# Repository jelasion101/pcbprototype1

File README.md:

Uses footprints sourced from Joe Scotto https://github.com/joe-scotto/, find sourced footprints at https://github.com/joe-scotto/scottokeebs

jelaskeyboard.kicad_pcb: KICAD PCB Design

jelaskeyboard.kicad_sch: KICAD Schematic Diagram + Footprints

jelaskeyboard.kicad_prl / jelaskeyboard.kicad_pro: Associated KICAD files

jelaskeyboard.zip: Built GBR ZIP file

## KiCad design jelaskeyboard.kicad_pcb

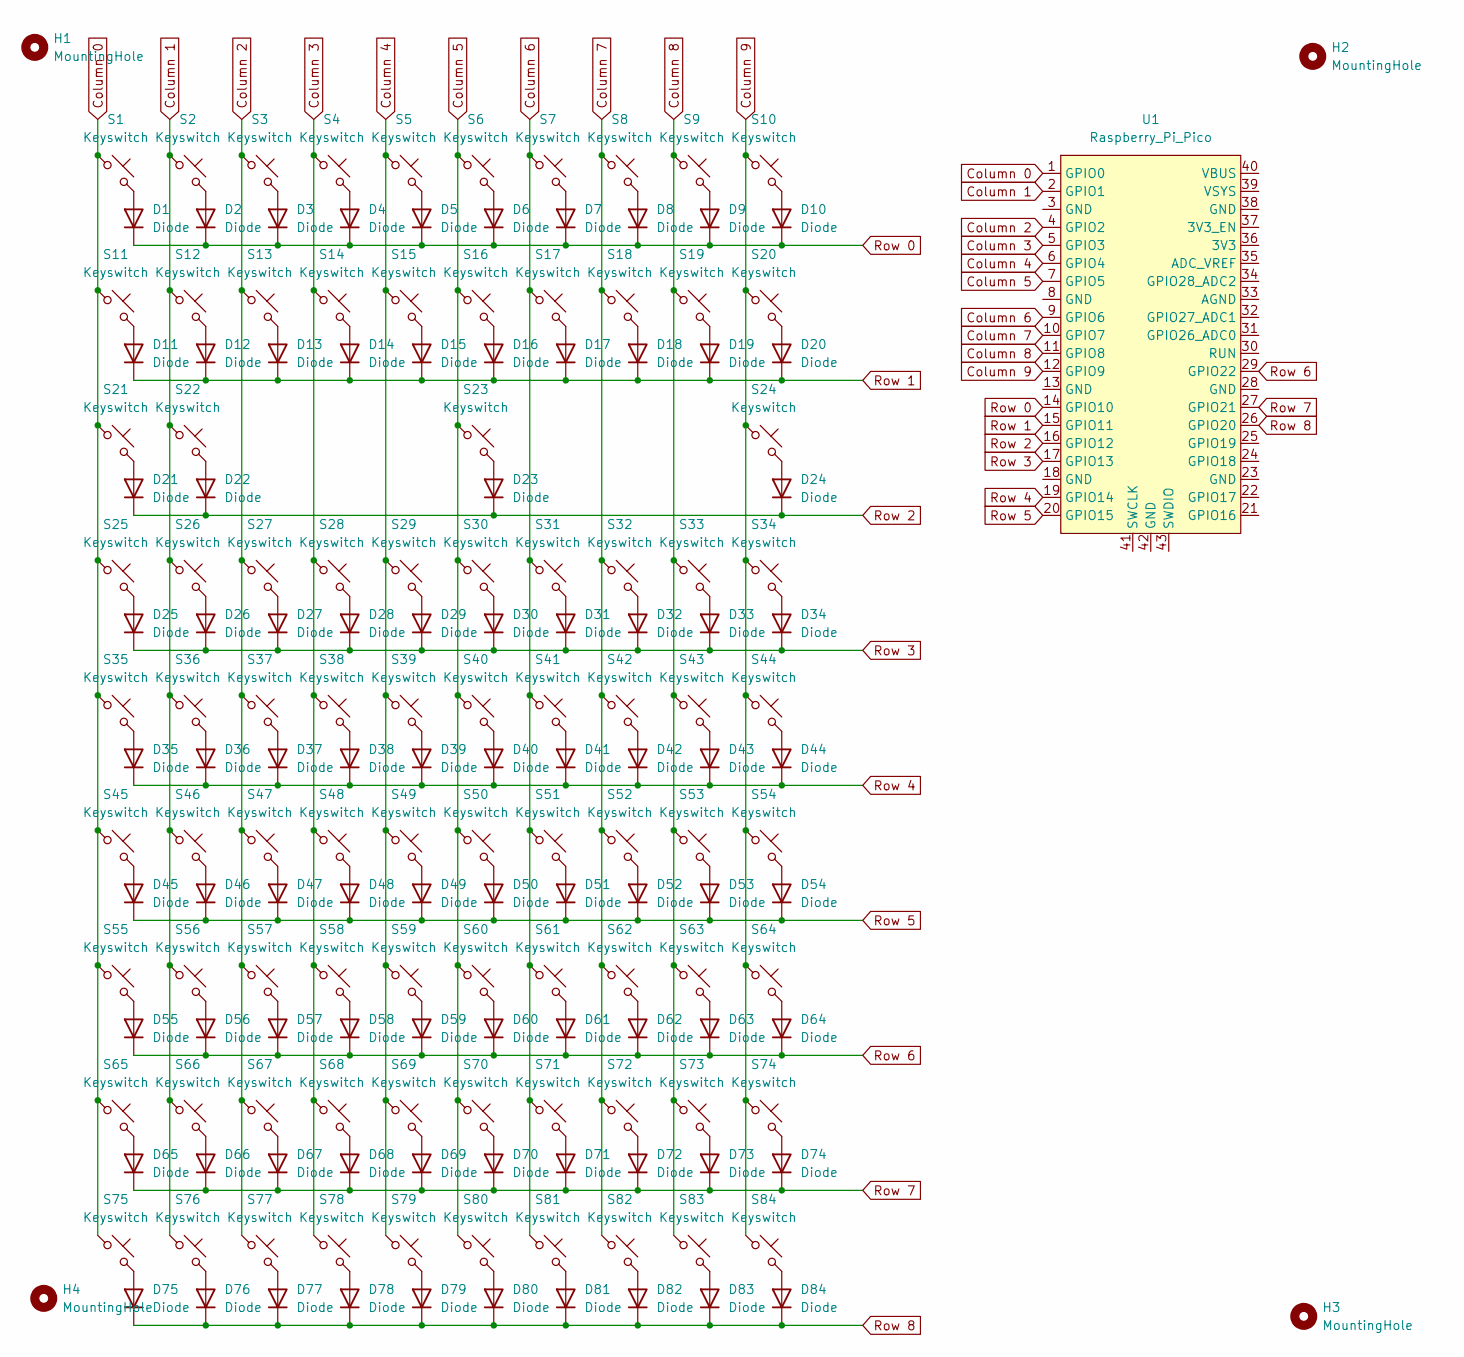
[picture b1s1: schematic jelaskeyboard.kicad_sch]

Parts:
D1, D2, D3, D4, D5, D6, D7, D8, D9, D10, D11, D12, D13, D14, D15, D16, D17, D18, D19, D20, D21, D22, D23, D24, D25, D26, D27, D28, D29, D30, D31, D32, D33, D34, D35, D36, D37, D38, D39, D40, D41, D42, D43, D44, D45, D46, D47, D48, D49, D50, D51, D52, D53, D54, D55, D56, D57, D58, D59, D60, D61, D62, D63, D64, D65, D66, D67, D68, D69, D70, D71, D72, D73, D74, D75, D76, D77, D78, D79, D80, D81, D82, D83, D84: Diode; Diode_DO-35
H1, H2, H3, H4: MountingHole; MountingHole_2.1mm
S1, S2, S3, S4, S5, S6, S7, S8, S9, S10, S11, S12, S13, S14, S15, S16, S17, S18, S19, S20, S22, S25, S26, S27, S28, S29, S30, S31, S32, S33, S34, S35, S36, S37, S38, S39, S40, S41, S42, S43, S44, S45, S46, S47, S48, S49, S50, S51, S52, S53, S54, S55, S56, S57, S58, S59, S60, S61, S62, S63, S64, S65, S66, S67, S68, S69, S70, S71, S72, S73, S74, S75, S76, S77, S78, S79, S80, S81, S82, S83, S84: Keyswitch; MX_PCB_1.00u
S21, S24: Keyswitch; MX_PCB_1.50u
S23: Keyswitch; MX_PCB_6.00u
U1: Raspberry_Pi_Pico

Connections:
Column 0: S1.1, S11.1, S21.1, S25.1, S35.1, S45.1, S55.1, S65.1, S75.1, U1.1 (GPIO0)
Column 1: S2.1, S12.1, S22.1, S26.1, S36.1, S46.1, S56.1, S66.1, S76.1, U1.2 (GPIO1)
Column 2: S3.1, S13.1, S27.1, S37.1, S47.1, S57.1, S67.1, S77.1, U1.4 (GPIO2)
Column 3: S4.1, S14.1, S28.1, S38.1, S48.1, S58.1, S68.1, S78.1, U1.5 (GPIO3)
Column 4: S5.1, S15.1, S29.1, S39.1, S49.1, S59.1, S69.1, S79.1, U1.6 (GPIO4)
Column 5: S6.1, S16.1, S23.1, S30.1, S40.1, S50.1, S60.1, S70.1, S80.1, U1.7 (GPIO5)
Column 6: S7.1, S17.1, S31.1, S41.1, S51.1, S61.1, S71.1, S81.1, U1.9 (GPIO6)
Column 7: S8.1, S18.1, S32.1, S42.1, S52.1, S62.1, S72.1, S82.1, U1.10 (GPIO7)
Column 8: S9.1, S19.1, S33.1, S43.1, S53.1, S63.1, S73.1, S83.1, U1.11 (GPIO8)
Column 9: S10.1, S20.1, S24.1, S34.1, S44.1, S54.1, S64.1, S74.1, S84.1, U1.12 (GPIO9)
unnamed: D1.2 (A), S1.2
unnamed: D2.2 (A), S2.2
unnamed: D3.2 (A), S3.2
unnamed: D4.2 (A), S4.2
unnamed: D5.2 (A), S5.2
unnamed: D6.2 (A), S6.2
unnamed: D7.2 (A), S7.2
unnamed: D8.2 (A), S8.2
unnamed: D9.2 (A), S9.2
unnamed: D10.2 (A), S10.2
unnamed: D11.2 (A), S11.2
unnamed: D12.2 (A), S12.2
unnamed: D13.2 (A), S13.2
unnamed: D14.2 (A), S14.2
unnamed: D15.2 (A), S15.2
unnamed: D16.2 (A), S16.2
unnamed: D17.2 (A), S17.2
unnamed: D18.2 (A), S18.2
unnamed: D19.2 (A), S19.2
unnamed: D20.2 (A), S20.2
unnamed: D21.2 (A), S21.2
unnamed: D22.2 (A), S22.2
unnamed: D23.2 (A), S23.2
unnamed: D24.2 (A), S24.2
unnamed: D25.2 (A), S25.2
unnamed: D26.2 (A), S26.2
unnamed: D27.2 (A), S27.2
unnamed: D28.2 (A), S28.2
unnamed: D29.2 (A), S29.2
unnamed: D30.2 (A), S30.2
unnamed: D31.2 (A), S31.2
unnamed: D32.2 (A), S32.2
unnamed: D33.2 (A), S33.2
unnamed: D34.2 (A), S34.2
unnamed: D35.2 (A), S35.2
unnamed: D36.2 (A), S36.2
unnamed: D37.2 (A), S37.2
unnamed: D38.2 (A), S38.2
unnamed: D39.2 (A), S39.2
unnamed: D40.2 (A), S40.2
unnamed: D41.2 (A), S41.2
unnamed: D42.2 (A), S42.2
unnamed: D43.2 (A), S43.2
unnamed: D44.2 (A), S44.2
unnamed: D45.2 (A), S45.2
unnamed: D46.2 (A), S46.2
unnamed: D47.2 (A), S47.2
unnamed: D48.2 (A), S48.2
unnamed: D49.2 (A), S49.2
unnamed: D50.2 (A), S50.2
unnamed: D51.2 (A), S51.2
unnamed: D52.2 (A), S52.2
unnamed: D53.2 (A), S53.2
unnamed: D54.2 (A), S54.2
unnamed: D55.2 (A), S55.2
unnamed: D56.2 (A), S56.2
unnamed: D57.2 (A), S57.2
unnamed: D58.2 (A), S58.2
unnamed: D59.2 (A), S59.2
unnamed: D60.2 (A), S60.2
unnamed: D61.2 (A), S61.2
unnamed: D62.2 (A), S62.2
unnamed: D63.2 (A), S63.2
unnamed: D64.2 (A), S64.2
unnamed: D65.2 (A), S65.2
unnamed: D66.2 (A), S66.2
unnamed: D67.2 (A), S67.2
unnamed: D68.2 (A), S68.2
unnamed: D69.2 (A), S69.2
unnamed: D70.2 (A), S70.2
unnamed: D71.2 (A), S71.2
unnamed: D72.2 (A), S72.2
unnamed: D73.2 (A), S73.2
unnamed: D74.2 (A), S74.2
unnamed: D75.2 (A), S75.2
unnamed: D76.2 (A), S76.2
unnamed: D77.2 (A), S77.2
unnamed: D78.2 (A), S78.2
unnamed: D79.2 (A), S79.2
unnamed: D80.2 (A), S80.2
unnamed: D81.2 (A), S81.2
unnamed: D82.2 (A), S82.2
unnamed: D83.2 (A), S83.2
unnamed: D84.2 (A), S84.2
Row 0: D1.1 (K), D2.1 (K), D3.1 (K), D4.1 (K), D5.1 (K), D6.1 (K), D7.1 (K), D8.1 (K), D9.1 (K), D10.1 (K), U1.14 (GPIO10)
Row 1: D11.1 (K), D12.1 (K), D13.1 (K), D14.1 (K), D15.1 (K), D16.1 (K), D17.1 (K), D18.1 (K), D19.1 (K), D20.1 (K), U1.15 (GPIO11)
Row 2: D21.1 (K), D22.1 (K), D23.1 (K), D24.1 (K), U1.16 (GPIO12)
Row 3: D25.1 (K), D26.1 (K), D27.1 (K), D28.1 (K), D29.1 (K), D30.1 (K), D31.1 (K), D32.1 (K), D33.1 (K), D34.1 (K), U1.17 (GPIO13)
Row 4: D35.1 (K), D36.1 (K), D37.1 (K), D38.1 (K), D39.1 (K), D40.1 (K), D41.1 (K), D42.1 (K), D43.1 (K), D44.1 (K), U1.19 (GPIO14)
Row 5: D45.1 (K), D46.1 (K), D47.1 (K), D48.1 (K), D49.1 (K), D50.1 (K), D51.1 (K), D52.1 (K), D53.1 (K), D54.1 (K), U1.20 (GPIO15)
Row 6: D55.1 (K), D56.1 (K), D57.1 (K), D58.1 (K), D59.1 (K), D60.1 (K), D61.1 (K), D62.1 (K), D63.1 (K), D64.1 (K), U1.29 (GPIO22)
Row 7: D65.1 (K), D66.1 (K), D67.1 (K), D68.1 (K), D69.1 (K), D70.1 (K), D71.1 (K), D72.1 (K), D73.1 (K), D74.1 (K), U1.27 (GPIO21)
Row 8: D75.1 (K), D76.1 (K), D77.1 (K), D78.1 (K), D79.1 (K), D80.1 (K), D81.1 (K), D82.1 (K), D83.1 (K), D84.1 (K), U1.26 (GPIO20)

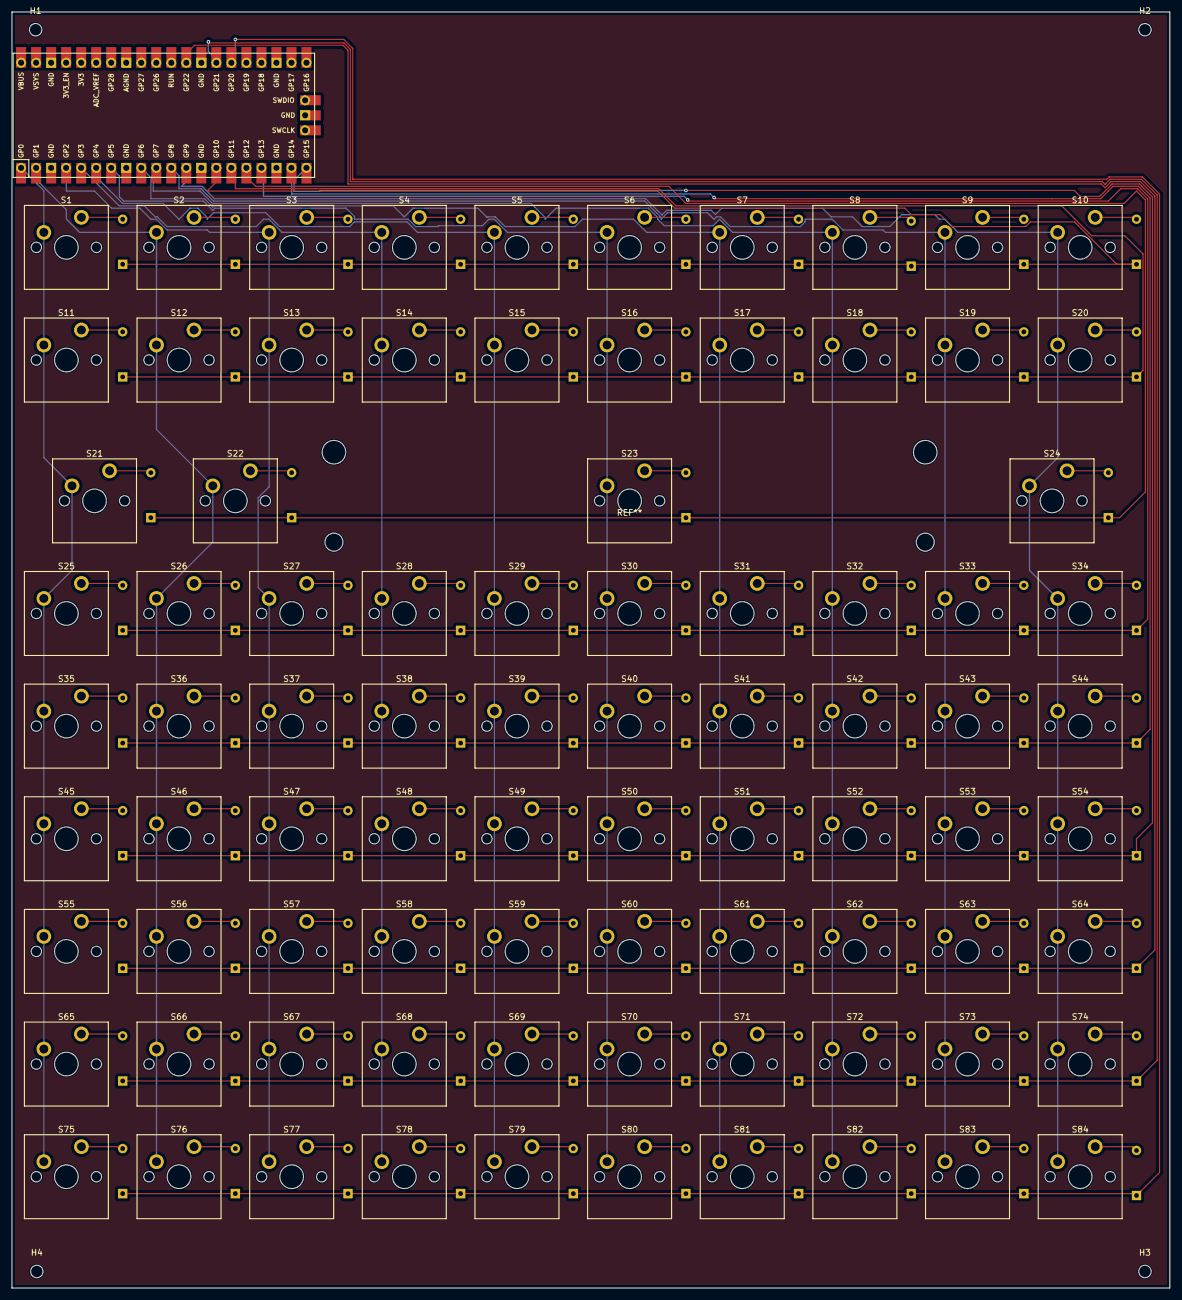
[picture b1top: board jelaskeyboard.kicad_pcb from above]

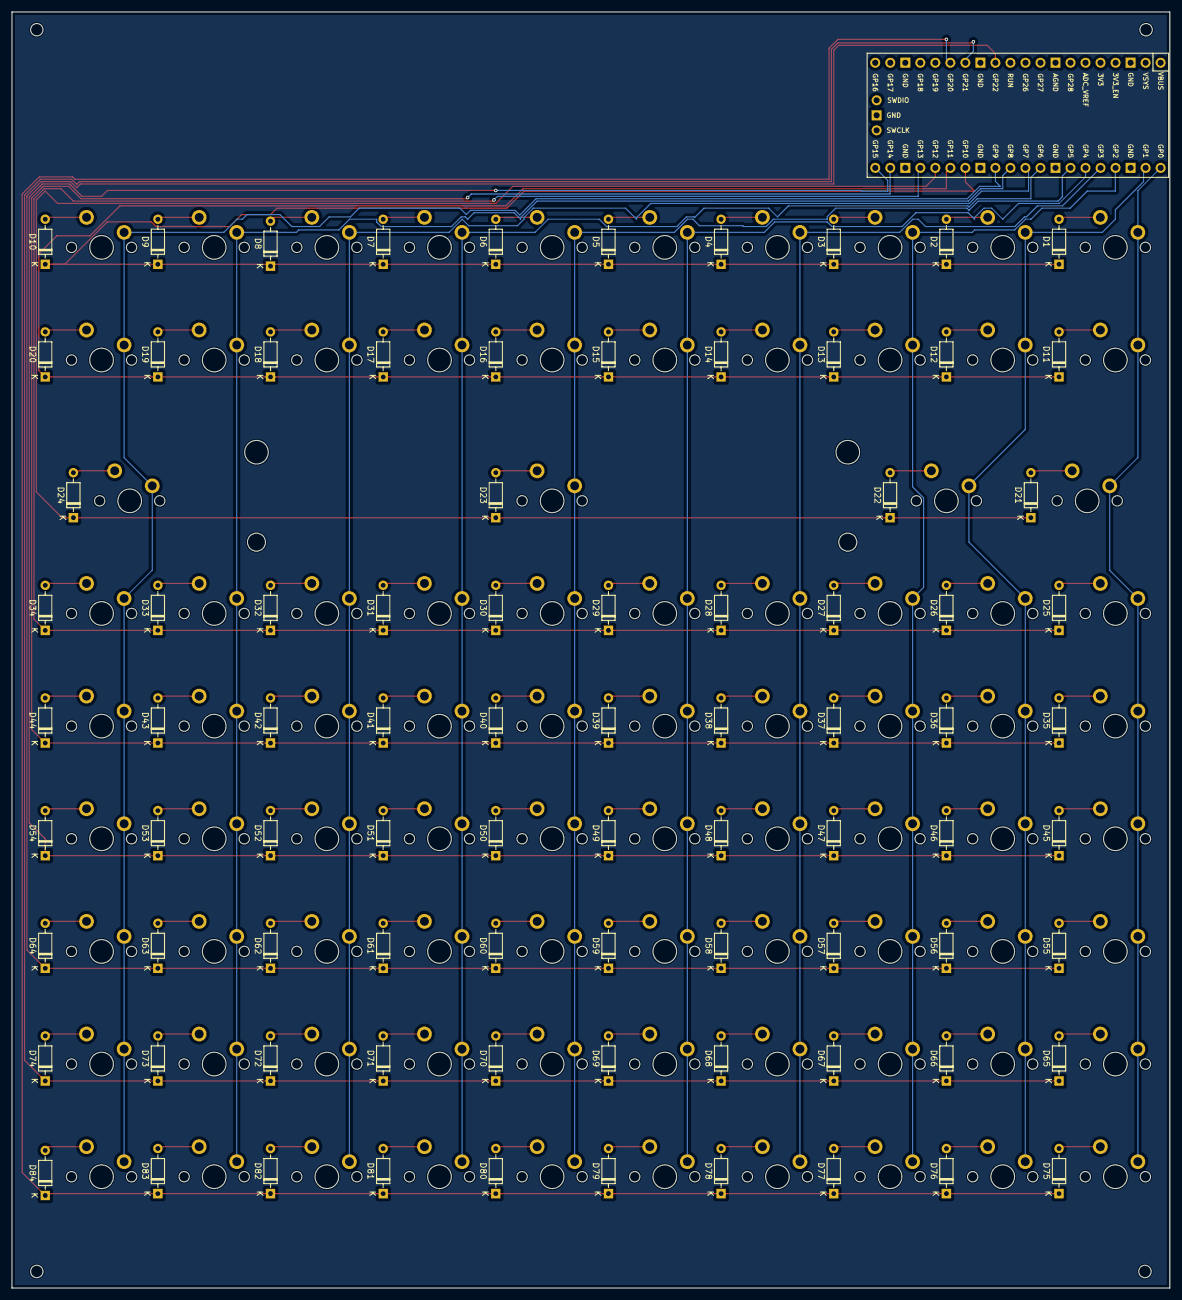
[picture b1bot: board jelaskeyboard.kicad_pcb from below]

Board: 2 copper layers, 195.8 x 215.8 mm, 173 parts (84 on the bottom side), 103 nets.

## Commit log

2024-03-26 uploaded original files
2024-03-26 Added additional KICAD files
2024-03-26 Update README.md
    reworded credits
